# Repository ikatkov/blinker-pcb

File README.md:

# Astable Oscillator Circuit 
There are many explanations online, [this one][1] is as good as any. A good question to ask yourself is - why does it oscilate?

I was curious how small I can go. On this board traces are 25mil. I found that this is already rather small and fiddly for the through hole components. Perhaps I'd just stop here. With signal traces I can probably go as low as 6-12mil, but physical size of not SMD component just keeps the board rather large.

Connectors are [JST-XHP][2], the rest is from [AliExpress][3]. Note that this is technically is a two layers PCB, there is a air-wire between C1 and Q1. I used a cut off resistor leg to make a bridge on the top level.

[1]: https://www.electronics-tutorials.ws/waveforms/astable.html
[2]: https://www.amazon.com/gp/product/B0774TF39N
[3]: https://www.aliexpress.com

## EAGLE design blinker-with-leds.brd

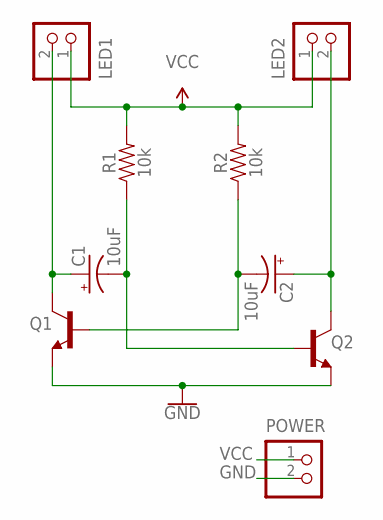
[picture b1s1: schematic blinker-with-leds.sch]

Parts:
C1, C2: 10uF; CPOL-RADIAL-2.5MM-5MM
LED1, LED2: B2B-XH-A
POWER: B2B-XH-A
Q1, Q2: 600mA/40V; TO-92
R1, R2: 10k; AXIAL-0.3

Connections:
GND: POWER.2, Q1.3 (E), Q2.3 (E)
LED1-GND: C1.1 (+), LED1.2, Q1.1 (C)
LED2-GND: C2.1 (+), LED2.2, Q2.1 (C)
Q1-BASE: C2.2 (-), Q1.2 (B), R2.P$1 (1)
Q2-BASE: C1.2 (-), Q2.2 (B), R1.P$1 (1)
VCC: LED1.1, LED2.1, POWER.1, R1.P$2 (2), R2.P$2 (2)

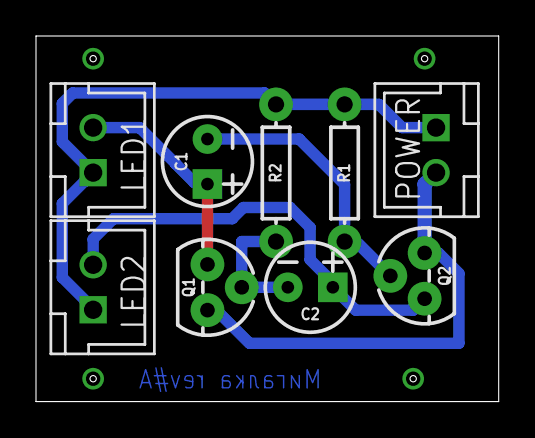
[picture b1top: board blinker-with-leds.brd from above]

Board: 2 copper layers, 25.7 x 20.3 mm, 9 parts (0 on the bottom side), 6 nets.

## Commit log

2019-04-08 Add images
2019-04-08 Add description
2019-04-08 Add photo
2019-04-08 Resized
2019-04-08 add real photo
2019-04-08 Added connector description
2019-04-08 More text

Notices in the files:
parts and their libraries:
SparkFun-Capacitors: Licensing: Creative Commons ShareAlike 4.0 International - https://creativecommons.org/licenses/by-sa/4.0
